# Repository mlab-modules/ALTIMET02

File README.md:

# ALTIMET02 - Precision Digital Pressure, temperature, and altimeter sensor

The [MLAB ALTIMET02](https://github.com/mlab-modules/ALTIMET02) is a high-performance pressure and temperature sensing module, based on the [MS561101BA03](https://www.te.com/usa-en/product-MS561101BA03-50.html) pressure sensor. This module is designed for use in a variety of applications, including meteorology, navigation, climate monitoring, and other scientific and industrial applications. 

## Specifications

The key component of the ALTIMET02 module is TE Connectivity MS561101BA03 sensor. This sensor is a highly accurate and low-power barometric sensor with a resolution of up to 10 cm. The sensor provides a 24-bit digital output via the I2C or SPI interfaces, allowing for easy integration with various microcontrollers.

### Parameters

* Pressure and Temperature measurement
* Pressure resolution: 10 cm
* Temperature resolution: 0.01°C
* Communication interface: I2C and SPI
* Supply voltage: 1.8V to 3.6V
* Power consumption: Low (<1uA during measurement)
* Full-scale pressure range: 10 - 1200 mbar
* Operating temperature range: -40 to +85 °C
* High reliability and long-term stability
* Advanced error compensation
* Enhanced EMI Protection

## Use Cases

The ALTIMET02 module is primarily designed as a pressure-sensing device for scientific experiments like statospheric balloons, but its capabilities extend far beyond this purpose. With high accuracy and low power consumption, the module is ideal for a wide range of applications.

### Atmospheric pressure and meteorological applications

As an atmospheric pressure sensor, ALTIMET02 is extremely suitable for meteorological applications. The module can be used for tracking pressure changes over time, which can provide valuable data for weather prediction. The combination of pressure and temperature measurements can help create a more detailed picture of atmospheric conditions.

### Altimetry and navigation

Altitude measurement is another key area where ALTIMET02 excels. Altitude measurement can be done using the barometric method, which uses the change in atmospheric pressure with altitude. This is useful for various types of navigation, including hiking, aviation, and marine navigation.

### Climate monitoring and scientific applications

ALTIMET02 is also a tool for scientific and industrial applications where it is important to monitor changes in climatic conditions. The module can be, for example, used in the field of scientific research to study climate change or in industry for monitoring and controlling conditions in various environments, such as greenhouses, warehouses, and production halls.

### Low power consumption applications

Due to its low power consumption, ALTIMET02 is suitable for applications that require long-term monitoring without frequent charging or battery replacement. This can include remote weather stations, animal trackers, or other portable devices.

## Connection to Microcontroller

The ALTIMET02 module can be easily connected to a microcontroller via the I2C or SPI interfaces.

For connecting the module to a microcontroller via the I2C interface, it is necessary to connect SDA (data line) and SCL (clock line) to the corresponding pins on the microcontroller.

For connection via the SPI interface, it is necessary to connect CSB (chip select), SDO (serial data output), SDI (serial data input), and SCLK (serial clock) to the corresponding pins on the microcontroller.

## Conclusion

The ALTIMET02 module is a highly accurate and low-power pressure and temperature

 sensing module, ideal for various applications. Its simple interface and small size allow for easy integration into any project. Its wide range of uses makes it an ideal solution for many different applications. For further information, please refer to the [ALTIMET02](https://github.com/mlab-modules/ALTIMET02) and the [MLAB website](https://www.mlab.cz/).

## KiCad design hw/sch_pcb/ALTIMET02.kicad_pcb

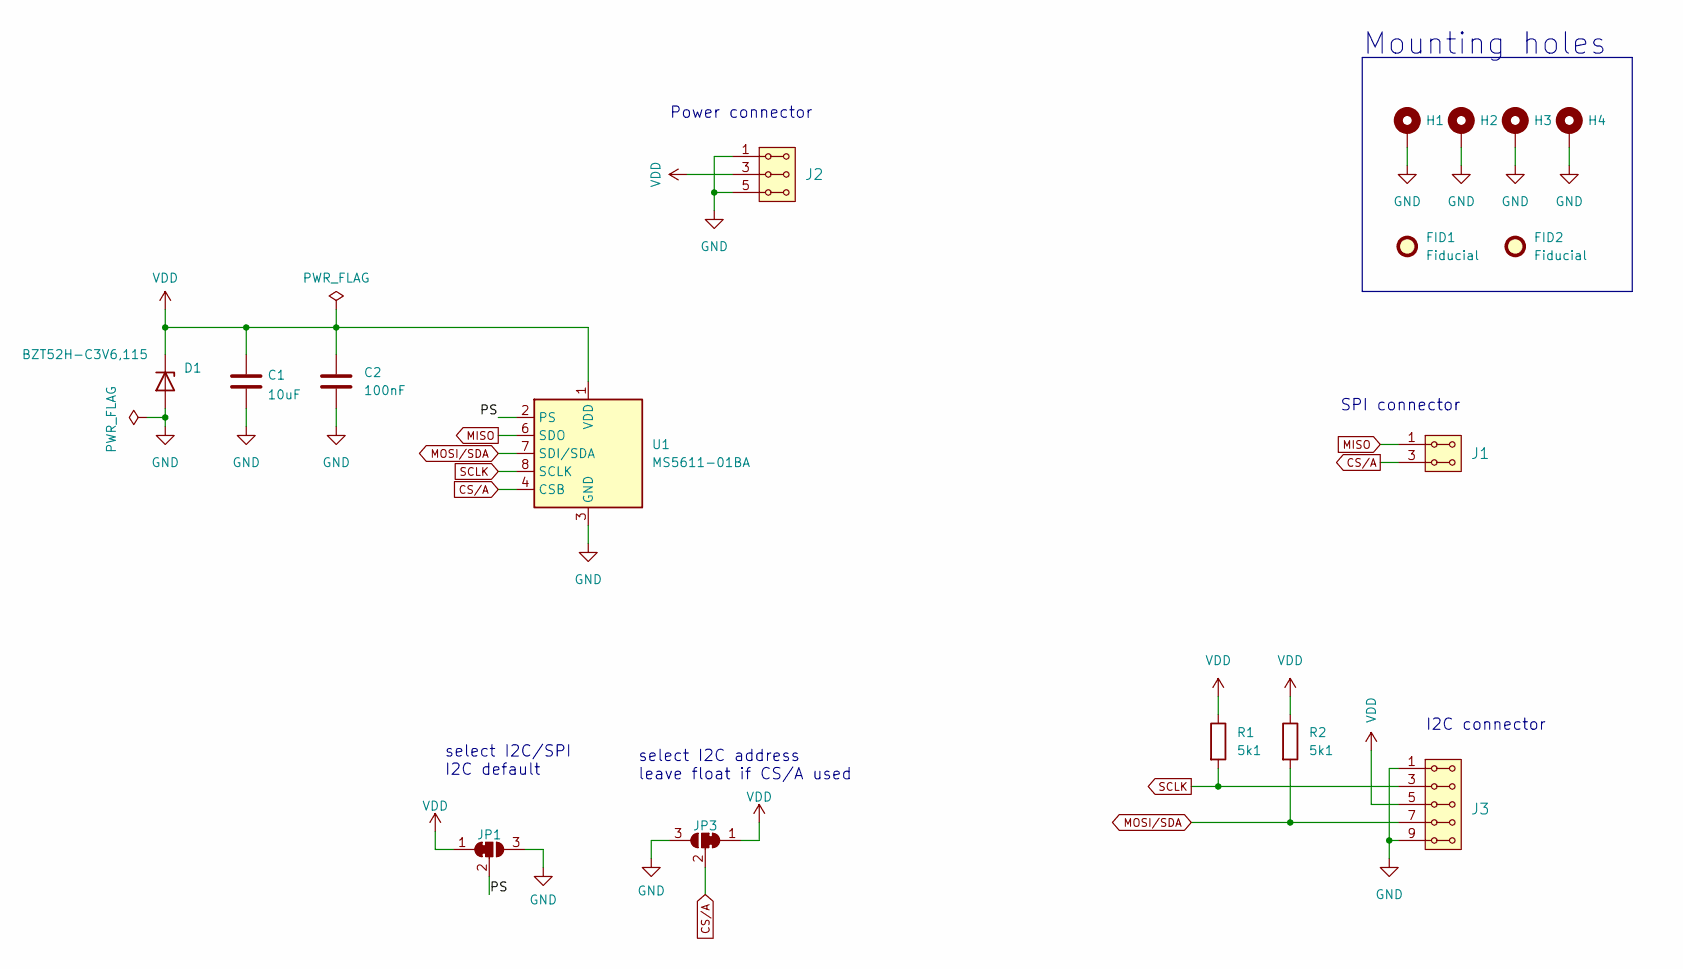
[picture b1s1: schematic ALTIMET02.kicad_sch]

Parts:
C1: 10uF; C_0805_2012Metric
C2: 100nF; C_0805_2012Metric
D1: BZT52H-C3V6,115; D_SOD-123F
FID1, FID2: Fiducial; Fiducial_1mm_Mask2mm
H1, H2, H3, H4: MountingHole_Pad; MountingHole_3mm
J1: HEADER_2x02_PARALLEL; Straight_2x02
J2: HEADER_2x03_PARALLEL; Straight_2x03
J3: HEADER_2x05_PARALLEL; Straight_2x05
JP1, JP3: SolderJumper_3_Bridged12; SolderJumper-3_P1.3mm_Bridged12_RoundedPad1.0x1.5mm_NumberL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
R1, R2: 5k1; R_0805_2012Metric
U1: MS5611-01BA; MS5611-01BA03

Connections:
/PS: JP1.2 (C), U1.2 (PS)
CS/A: J1.3, J1.4, JP3.2 (C), U1.4 (CSB), U1.5 (CSB)
GND: C1.2, C2.2, D1.2 (A), H1.1, H2.1, H3.1, H4.1, J2.1, J2.2, J2.5, J2.6, J3.1, J3.2, J3.9, J3.10, JP1.3 (B), JP3.3 (B), U1.3 (GND)
MISO: J1.1, J1.2, U1.6 (SDO)
MOSI/SDA: J3.7, J3.8, R2.2, U1.7 (SDI/SDA)
SCLK: J3.3, J3.4, R1.2, U1.8 (SCLK)
VDD: C1.1, C2.1, D1.1 (K), J2.3, J2.4, J3.5, J3.6, JP1.1 (A), JP3.1 (A), R1.1, R2.1, U1.1 (VDD)

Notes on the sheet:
select I2C/SPI I2C default
Mounting holes
SPI connector
Power connector
select I2C address leave float if CS/A used
I2C connector

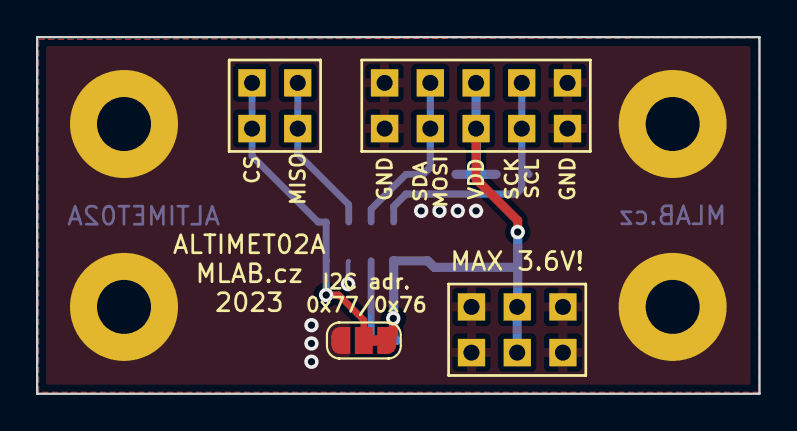
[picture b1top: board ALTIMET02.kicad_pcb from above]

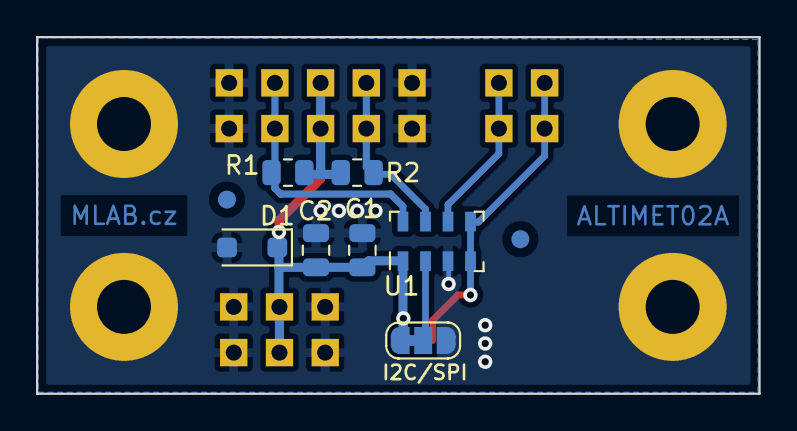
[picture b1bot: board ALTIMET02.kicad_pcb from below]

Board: 2 copper layers, 40.1 x 19.8 mm, 17 parts (9 on the bottom side), 7 nets.

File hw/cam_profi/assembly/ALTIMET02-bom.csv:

Component,Description,Part,References,Value,Footprint,Quantity Per PCB,Datasheet
1,Unpolarized capacitor,C,C2,100nF,C_0805_2012Metric,1,~
2,Unpolarized capacitor,C,C1,10uF,C_0805_2012Metric,1,~
3,Zener diode,D_Zener,D1,BZV55C3V6,Diode-MiniMELF_Standard,1,~
4,"2x02 2.54 mm pitch header, 2 pins next to each other are connected",HEADER_2x02_PARALLEL,J1,HEADER_2x02_PARALLEL,Straight_2x02,1,
5,"2x03 2.54 mm pitch header, 2 pins next to each other are connected",HEADER_2x03_PARALLEL,J2,HEADER_2x03_PARALLEL,Straight_2x03,1,
6,"2x05 2.54 mm pitch header, 2 pins next to each other are connected",HEADER_2x05_PARALLEL,J3,HEADER_2x05_PARALLEL,Straight_2x05,1,
7,"Barometric pressure sensor, 10cm resolution, 10 to 1200 mbar, I2C and SPI interface up to 20MHz, LGA-8",MS5611-01BA,U1,MS5611-01BA,LGA-8_3x5mm_P1.25mm,1,https://www.te.com/commerce/DocumentDelivery/DDEController?A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

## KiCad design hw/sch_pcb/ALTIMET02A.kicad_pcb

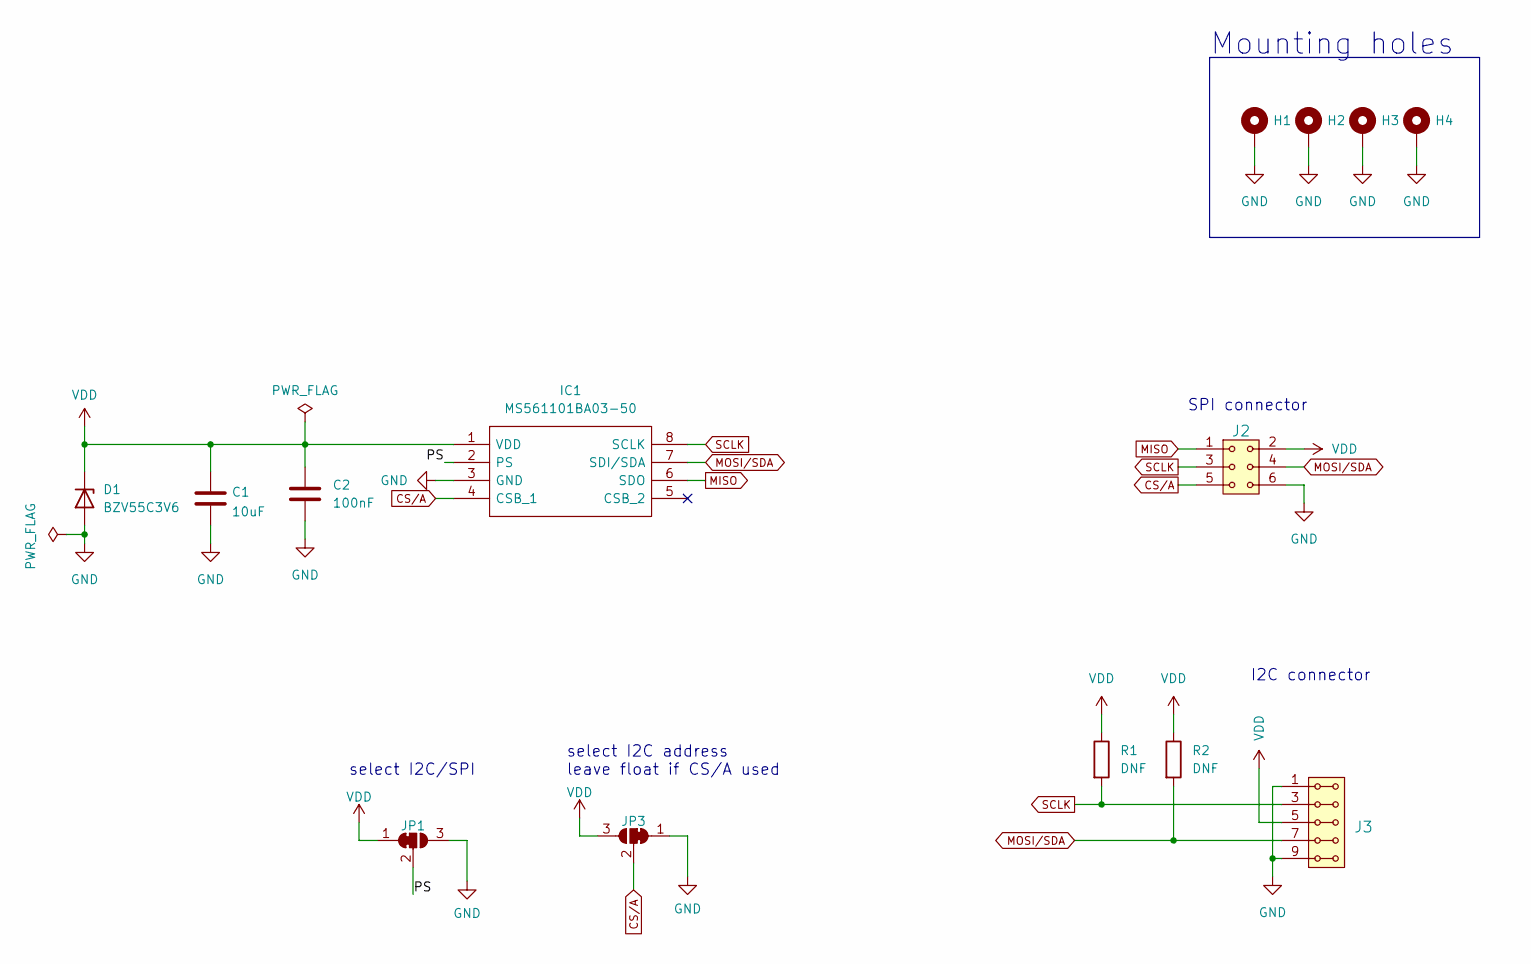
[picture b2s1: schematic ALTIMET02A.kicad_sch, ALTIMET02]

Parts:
C1: 10uF; C_0805_2012Metric
C2: 100nF; C_0805_2012Metric
D1: BZV55C3V6; Diode-MiniMELF_Standard
H1, H2, H3, H4: MountingHole_Pad; MountingHole_3mm
IC1: MS561101BA03-50; Mouser Part Number 824-MS561101BA03-50
J2: HEADER_2x03; Straight_2x03
J3: HEADER_2x05_PARALLEL; Straight_2x05
JP1, JP3: SolderJumper_3_Bridged12; SolderJumper-3_P1.3mm_Bridged12_RoundedPad1.0x1.5mm_NumberL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
R1, R2: DNF; R_0805_2012Metric

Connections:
/PS: IC1.2 (PS), JP1.2 (C)
CS/A: IC1.4 (CSB_1), J2.5, JP3.2 (C)
GND: C1.2, C2.2, D1.2 (A), H1.1, H2.1, H3.1, H4.1, IC1.3 (GND), J2.6, J3.1, J3.2, J3.9, J3.10, JP1.3 (B), JP3.1 (A)
MISO: IC1.6 (SDO), J2.1
MOSI/SDA: IC1.7 (SDI/SDA), J2.4, J3.7, J3.8, R2.2
SCLK: IC1.8 (SCLK), J2.3, J3.3, J3.4, R1.2
VDD: C1.1, C2.1, D1.1 (K), IC1.1 (VDD), J2.2, J3.5, J3.6, JP1.1 (A), JP3.3 (B), R1.1, R2.1

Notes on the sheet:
select I2C/SPI
Mounting holes
SPI connector
select I2C address leave float if CS/A used
I2C connector

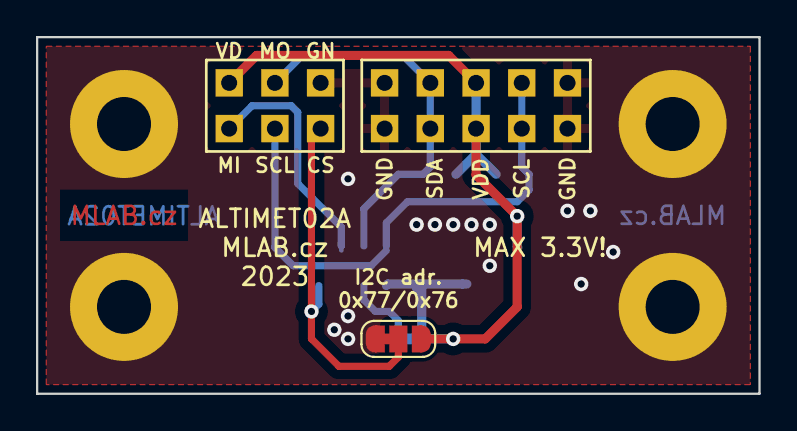
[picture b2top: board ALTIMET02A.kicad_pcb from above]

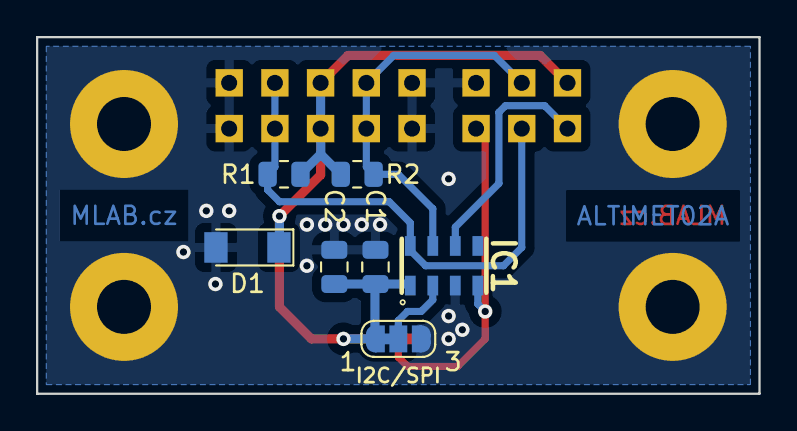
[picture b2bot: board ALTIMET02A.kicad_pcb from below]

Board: 2 copper layers, 40.1 x 19.8 mm, 14 parts (7 on the bottom side), 7 nets.

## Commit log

2023-01-12 Add files via upload
    KiCAD schematics
2023-01-12 Edit schema.
2023-01-16 pcb layout
2023-01-16 DNF values added
2023-01-17 3x1 layout
2023-01-18 Change directory structure.
2023-01-18 Fix title block.
2023-01-18 Update actions products
2023-01-18 Update assets submodule.
2023-01-18 Update version of kibot, swithch to upstream.
2023-01-18 Explicit name of kicad project files.
2023-01-18 Add pwr_flags to resolve ERC issues.
2023-01-18 Fix duplicate PWR_Flag Update symbols from libraries.
2023-01-19 GND via added
2023-01-19 Layout and silkscreen improvements.
2023-01-19 power header deleted, i2c/spi solder jumper moved to the back side, i2c addr. added
2023-01-20 Improve layout and silkscreen.
2023-02-12 Update submodule Fix CLK in silkscreen.
2023-02-12 Update worflow rename KiCAD project.
2023-02-12 Update metadata files
2023-02-13 Update workflow files
2023-05-25 automated commit; add github actions
2023-07-05 automated commit; rename source files to new naming convence
2023-09-06 power connector added, SPI and I2C connectors modified, default I2C adrress changed
2023-09-06 minor changes in layout, change diode
2023-09-06 add fiducial
2023-09-07 Fix sharp trace. Improve silkscreen.
2023-09-16 Update status
2023-09-20 update submodule
2023-09-20 add ustid
2023-09-20 resave
2023-09-21 Upravy a kontrola pred vyrobou
2023-09-22 Uprava PCB a kontrola UST_ID
2023-09-26 Update README.md
    Enlarge images on readme page.
2023-10-04 Edit B.Fab
2023-10-18 add test code
